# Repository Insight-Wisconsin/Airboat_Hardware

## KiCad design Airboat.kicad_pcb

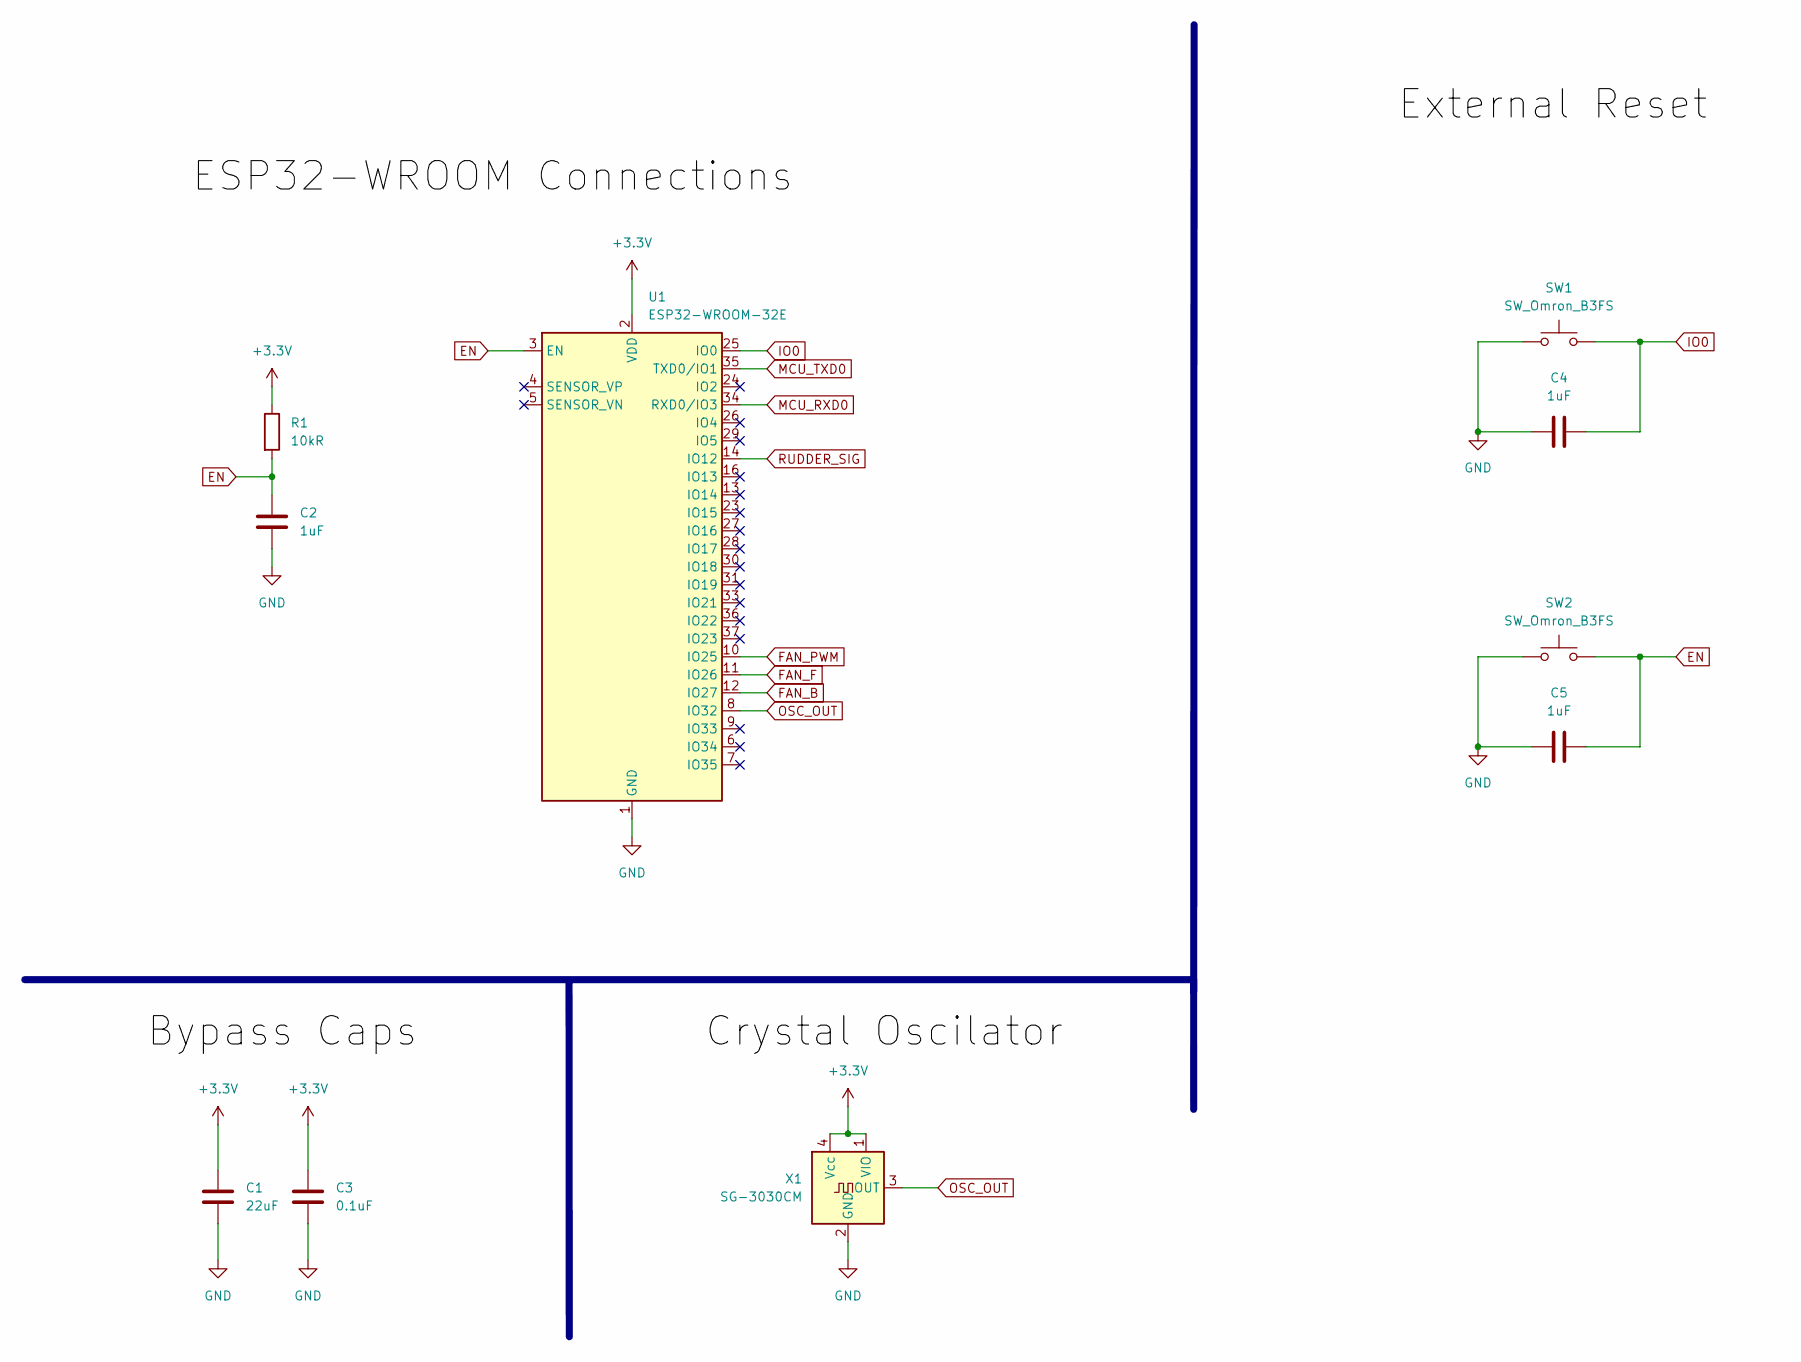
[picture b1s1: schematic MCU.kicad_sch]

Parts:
C1: 22uF; C_0603_1608Metric_Pad1.08x0.95mm_HandSolder
C2, C4, C5: 1uF; C_0603_1608Metric_Pad1.08x0.95mm_HandSolder
C3: 0.1uF; C_0603_1608Metric_Pad1.08x0.95mm_HandSolder
R1: 10kR; R_0603_1608Metric_Pad0.98x0.95mm_HandSolder
SW1, SW2: SW_Omron_B3FS; SW_SPST_Omron_B3FS-100xP
U1: ESP32-WROOM-32E; ESP32-WROOM-32D
X1: SG-3030CM; Oscillator_SMD_SeikoEpson_SG3030CM

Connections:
+3.3V: C1.1, C3.1, R1.1, U1.2 (VDD), X1.1 (VIO), X1.4 (Vcc); also elsewhere on the board
EN: C2.1, C5.2, R1.2, SW2.2, U1.3 (EN); also elsewhere on the board
FAN_B: U1.12 (IO27); also elsewhere on the board
FAN_F: U1.11 (IO26); also elsewhere on the board
FAN_PWM: U1.10 (IO25); also elsewhere on the board
GND: C1.2, C2.2, C3.2, C4.1, C5.1, SW1.1, SW2.1, U1.1 (GND), U1.15 (GND), U1.38 (GND), U1.39 (GND), X1.2 (GND); also elsewhere on the board
IO0: C4.2, SW1.2, U1.25 (IO0); also elsewhere on the board
MCU_RXD0: U1.34 (RXD0/IO3); also elsewhere on the board
MCU_TXD0: U1.35 (TXD0/IO1); also elsewhere on the board
OSC_OUT: U1.8 (IO32), X1.3 (OUT)
RUDDER_SIG: U1.14 (IO12); also elsewhere on the board

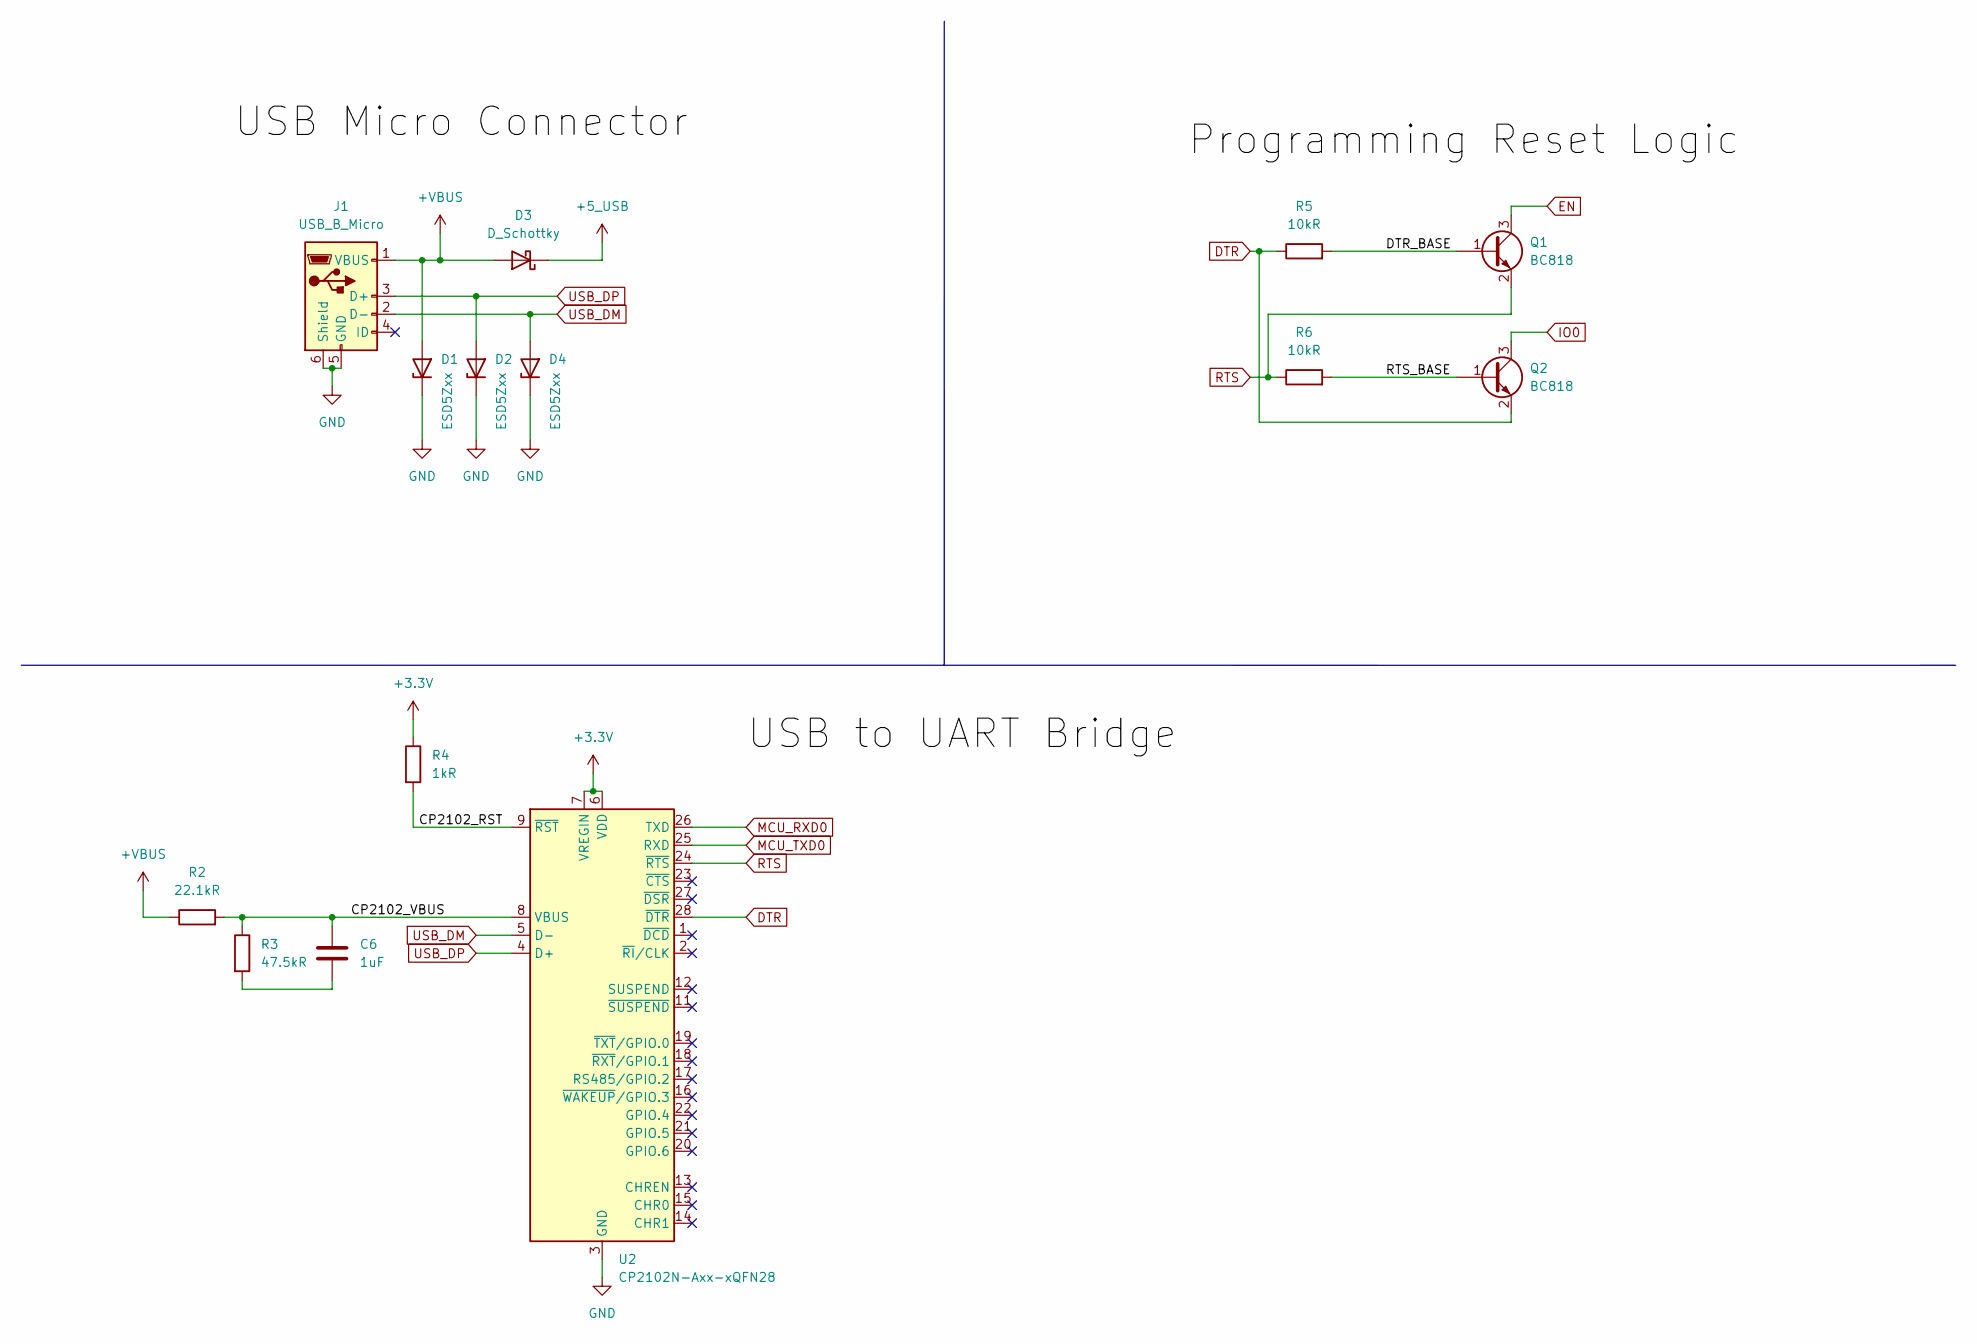
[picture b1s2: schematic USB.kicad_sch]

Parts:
C6: 1uF; C_0603_1608Metric_Pad1.08x0.95mm_HandSolder
D1, D2, D4: ESD5Zxx; D_SOD-523
D3: D_Schottky; D_SMC
J1: USB_B_Micro; USB_Micro-B_GCT_USB3076-30-A
Q1, Q2: BC818; SOT-23
R2: 22.1kR; R_0603_1608Metric_Pad0.98x0.95mm_HandSolder
R3: 47.5kR; R_0603_1608Metric_Pad0.98x0.95mm_HandSolder
R4: 1kR; R_0603_1608Metric_Pad0.98x0.95mm_HandSolder
R5, R6: 10kR; R_0603_1608Metric_Pad0.98x0.95mm_HandSolder
U2: CP2102N-Axx-xQFN28; QFN-28-1EP_5x5mm_P0.5mm_EP3.75x3.75mm

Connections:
+3.3V: R4.1, U2.6 (VDD), U2.7 (VREGIN); also elsewhere on the board
+5_USB: D3.1 (K); also elsewhere on the board
+VBUS: D1.2 (A), D3.2 (A), J1.1 (VBUS), R2.1
/USB/CP2102_RST: R4.2, U2.9 (~RST)
/USB/CP2102_VBUS: C6.1, R2.2, R3.1, U2.8 (VBUS)
/USB/DTR_BASE: Q1.1 (B), R5.2
/USB/RTS_BASE: Q2.1 (B), R6.2
DTR: Q2.2 (E), R5.1, U2.28 (~DTR)
EN: Q1.3 (C); also elsewhere on the board
GND: D1.1 (K), D2.1 (K), D4.1 (K), J1.5 (GND), J1.6 (Shield), U2.3 (GND), U2.29 (GND); also elsewhere on the board
IO0: Q2.3 (C); also elsewhere on the board
MCU_RXD0: U2.26 (TXD); also elsewhere on the board
MCU_TXD0: U2.25 (RXD); also elsewhere on the board
unnamed: C6.2, R3.2
RTS: Q1.2 (E), R6.1, U2.24 (~RTS)
USB_DM: D4.2 (A), J1.2 (D-), U2.5 (D-)
USB_DP: D2.2 (A), J1.3 (D+), U2.4 (D+)

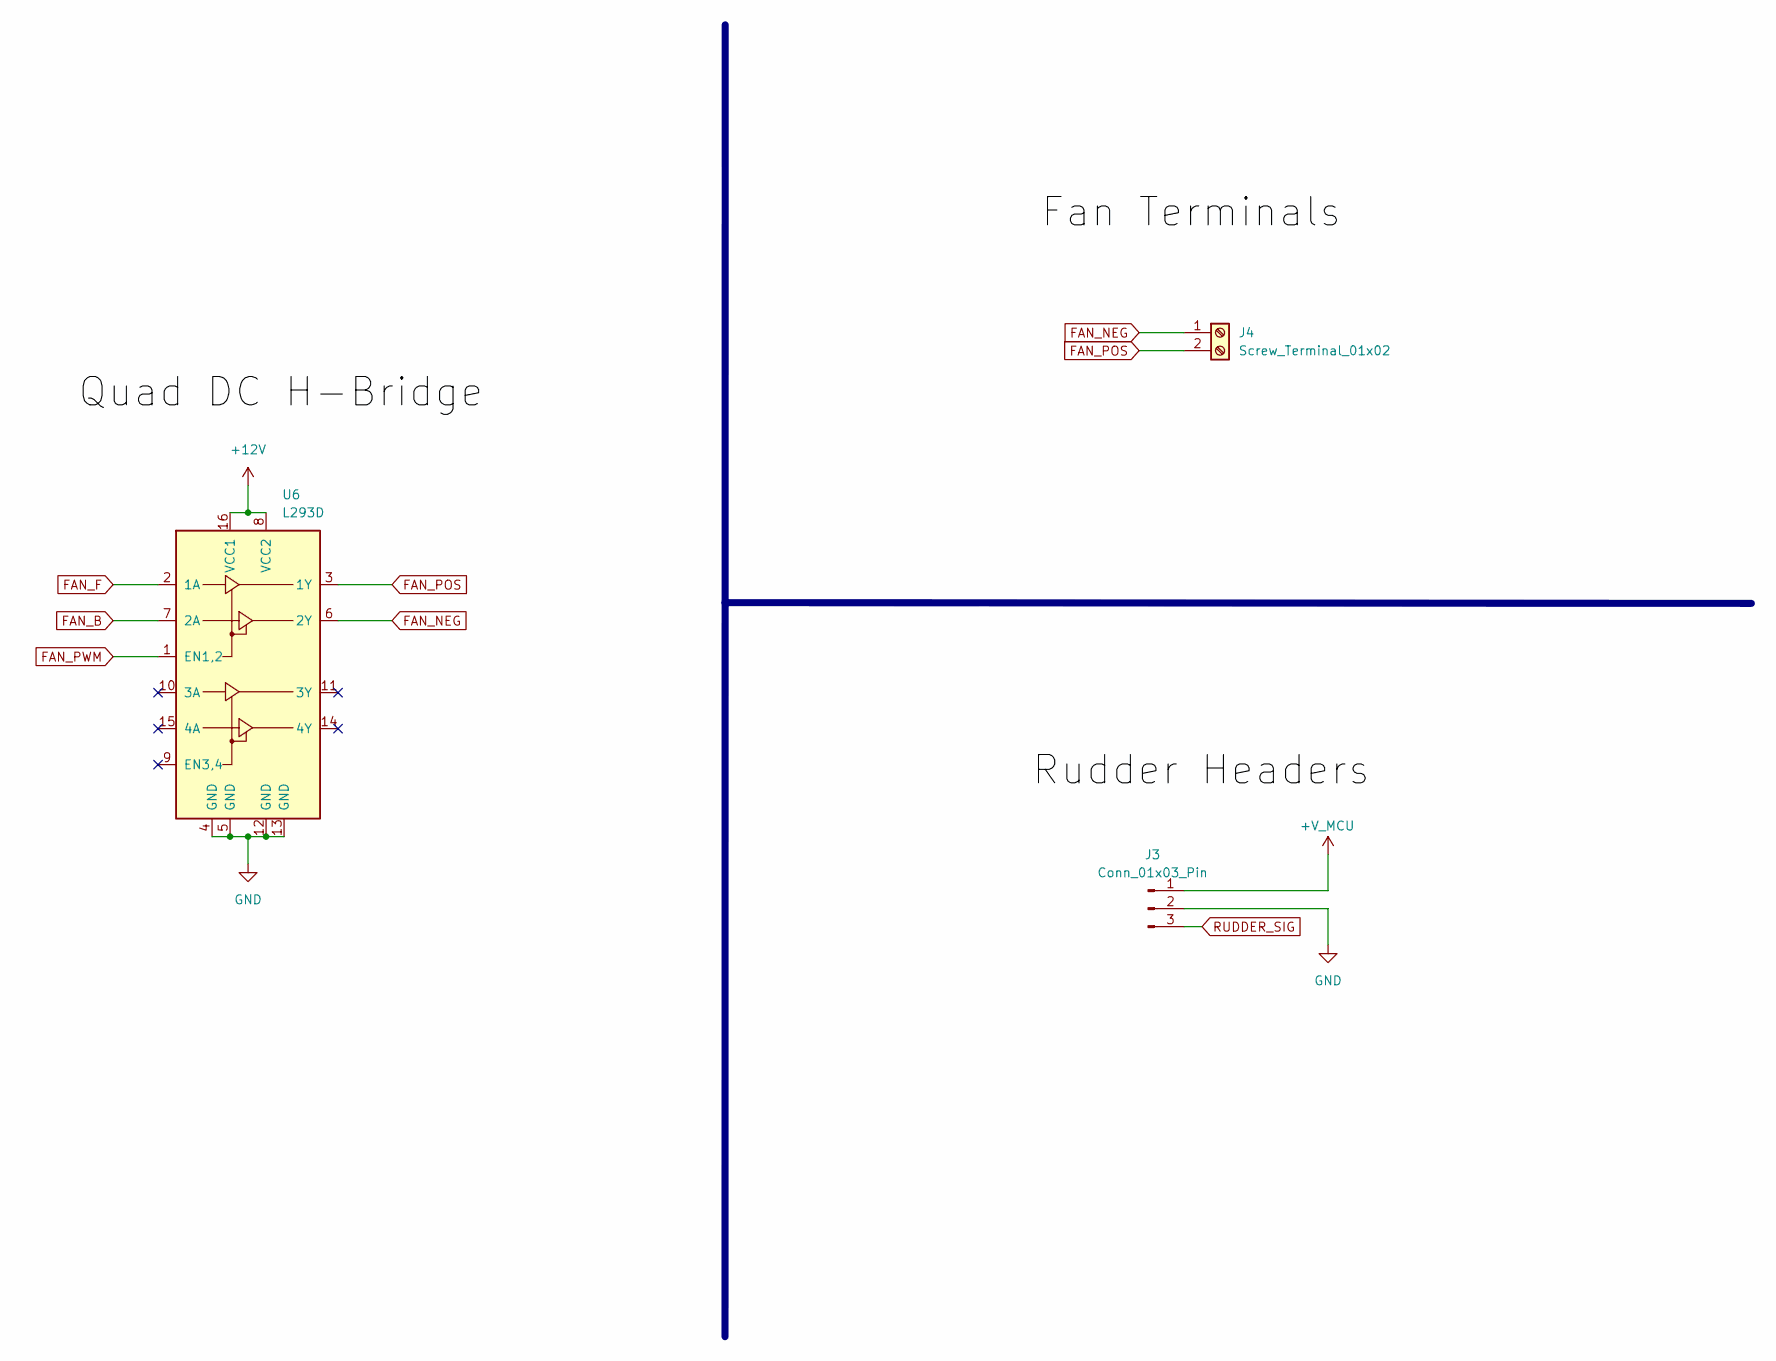
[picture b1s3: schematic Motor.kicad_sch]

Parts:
J3: Conn_01x03_Pin; FanPinHeader_1x03_P2.54mm_Vertical
J4: Screw_Terminal_01x02; TerminalBlock_Altech_AK300-2_P5.00mm
U6: L293D; DIP-16_W7.62mm

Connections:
+12V: U6.8 (VCC2), U6.16 (VCC1); also elsewhere on the board
+V_MCU: J3.1; also elsewhere on the board
FAN_B: U6.7 (2A); also elsewhere on the board
FAN_F: U6.2 (1A); also elsewhere on the board
FAN_NEG: J4.1, U6.6 (2Y)
FAN_POS: J4.2, U6.3 (1Y)
FAN_PWM: U6.1 (EN1,2); also elsewhere on the board
GND: J3.2, U6.4 (GND), U6.5 (GND), U6.12 (GND), U6.13 (GND); also elsewhere on the board
RUDDER_SIG: J3.3; also elsewhere on the board

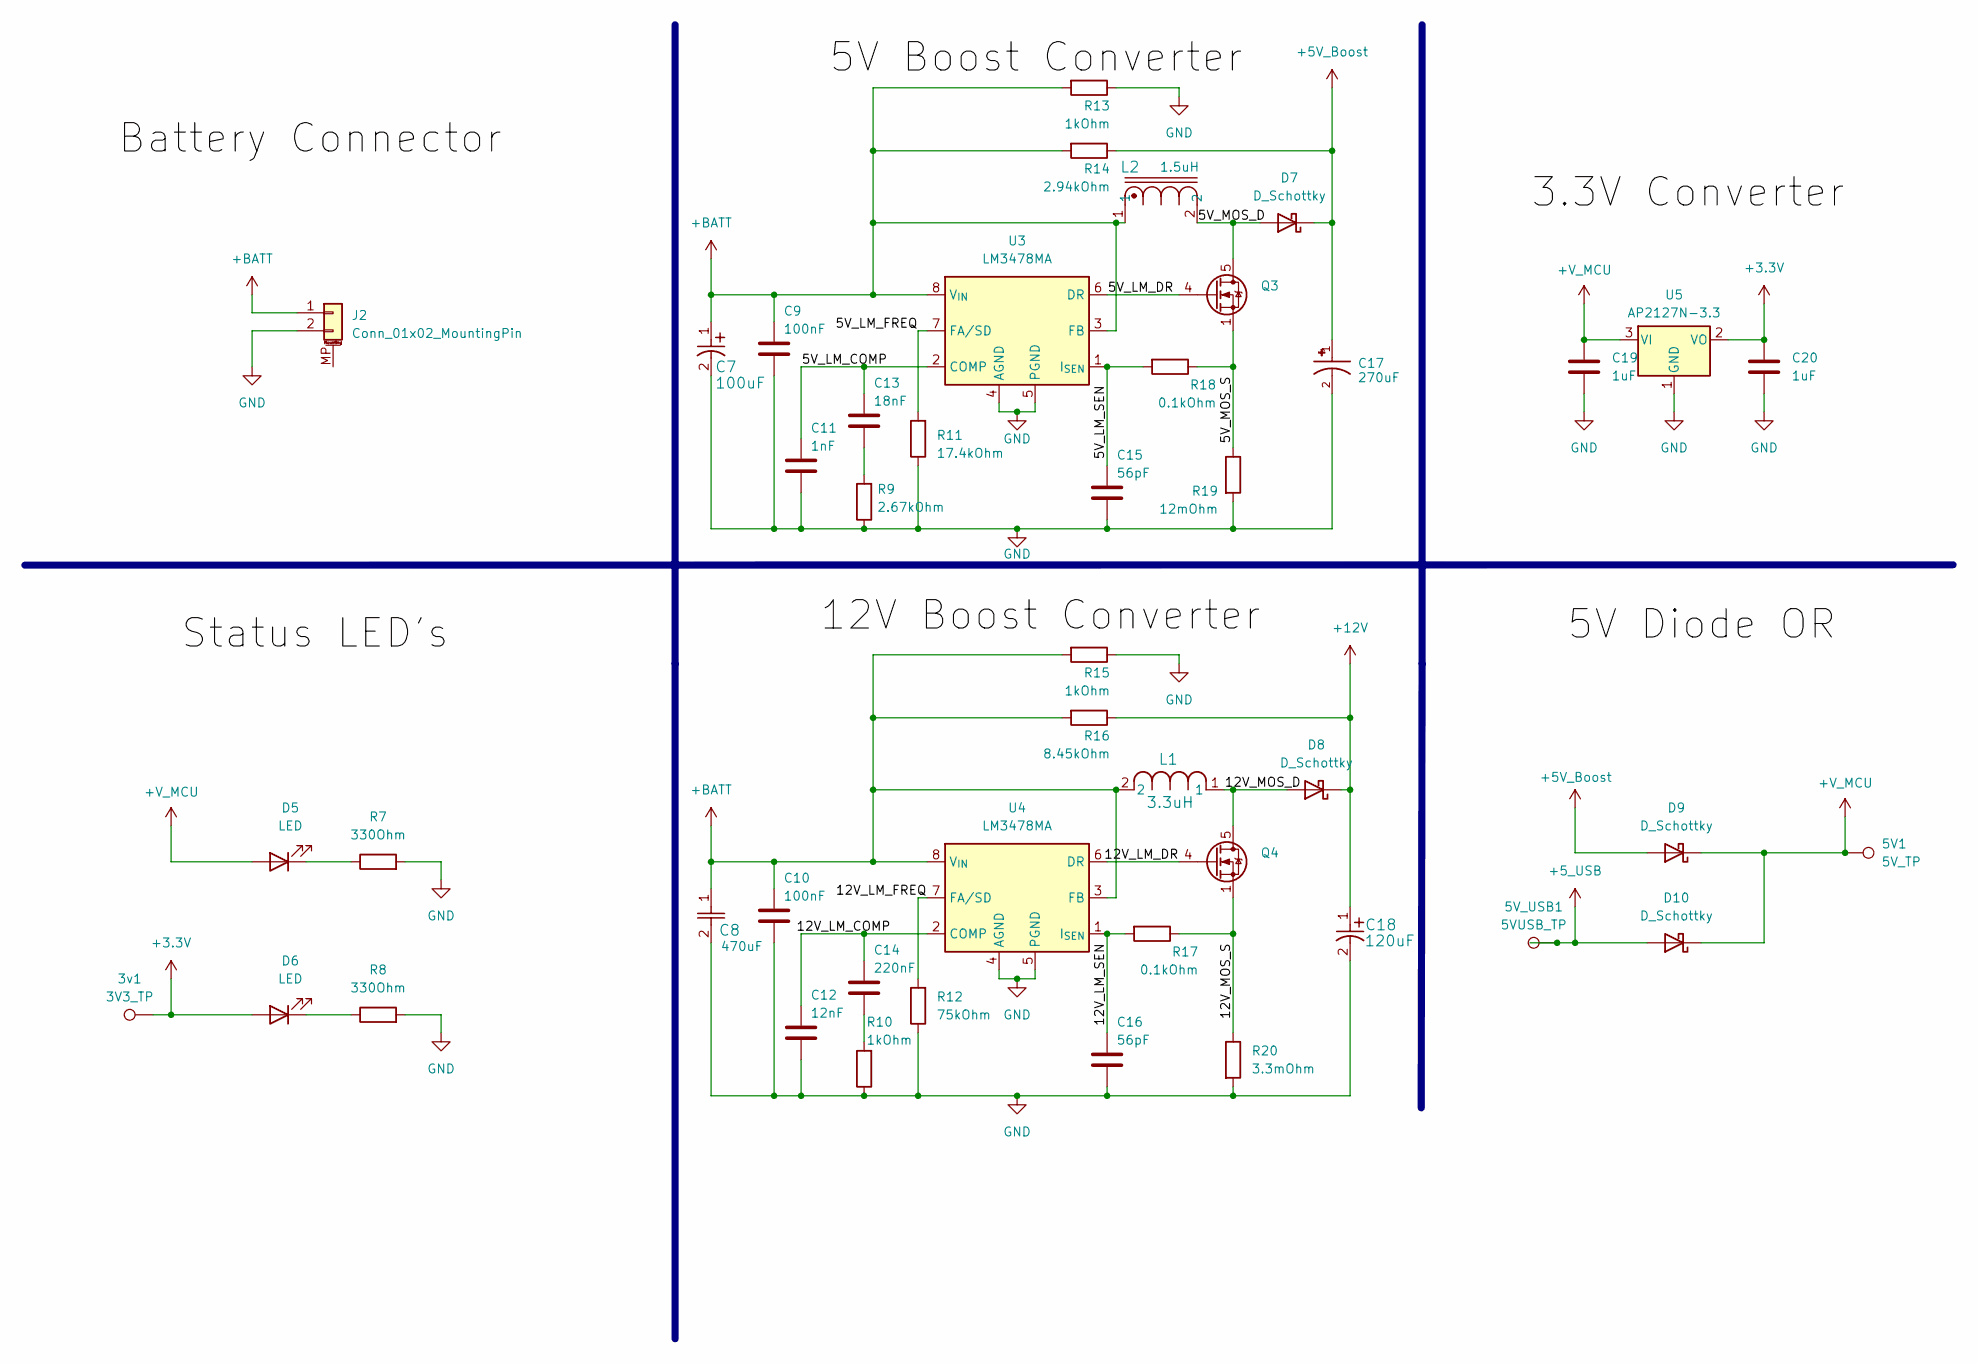
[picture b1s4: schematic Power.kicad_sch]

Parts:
3v1: 3V3_TP; TestPoint_Pad_D2.0mm
5V1: 5V_TP; TestPoint_Pad_D2.0mm
5V_USB1: 5VUSB_TP; TestPoint_Pad_D2.0mm
C7: T520A107M006ATE025; CAPMP3.4X1.6_1.8N_KEM
C8: UUD1E471MNL1GS; U2-R_NCH
C9, C10: 100nF; C_0603_1608Metric_Pad1.08x0.95mm_HandSolder
C11: 1nF; C_0603_1608Metric_Pad1.08x0.95mm_HandSolder
C12: 12nF; C_0603_1608Metric_Pad1.08x0.95mm_HandSolder
C13: 18nF; C_0603_1608Metric_Pad1.08x0.95mm_HandSolder
C14: 220nF; C_0603_1608Metric_Pad1.08x0.95mm_HandSolder
C15, C16: 56pF; C_0603_1608Metric_Pad1.08x0.95mm_HandSolder
C17: 16SVPG270M; CAP_16SVPG270M; PARTREV 05-Mar-21
C18: 20SVPF120M; PCAP_SVP_C6_PAN
C19, C20: 1uF; C_0603_1608Metric_Pad1.08x0.95mm_HandSolder
D5, D6: LED; LED_0805_2012Metric_Pad1.15x1.40mm_HandSolder
D7, D8, D9, D10: D_Schottky; D_SMC
J2: Conn_01x02_MountingPin; Hirose_DF3EA-02P-2H_1x02-1MP_P2.00mm_Horizontal
L1: IHLP6767GZER3R3M51; IND_IHLP-6767GZ_VIS
L2: DR1040-1R5-R; DR1040
Q3, Q4: CSD16321Q5; TDSON-8-1
R7, R8: 330Ohm; R_0603_1608Metric_Pad0.98x0.95mm_HandSolder
R9: 2.67kOhm; R_0603_1608Metric_Pad0.98x0.95mm_HandSolder
R10, R13, R15: 1kOhm; R_0603_1608Metric_Pad0.98x0.95mm_HandSolder
R11: 17.4kOhm; R_0603_1608Metric_Pad0.98x0.95mm_HandSolder
R12: 75kOhm; R_0603_1608Metric_Pad0.98x0.95mm_HandSolder
R14: 2.94kOhm; R_0603_1608Metric_Pad0.98x0.95mm_HandSolder
R16: 8.45kOhm; R_0603_1608Metric_Pad0.98x0.95mm_HandSolder
R17, R18: 0.1kOhm; R_0603_1608Metric_Pad0.98x0.95mm_HandSolder
R19: 12mOhm; R_0603_1608Metric_Pad0.98x0.95mm_HandSolder
R20: 3.3mOhm; R_2512_6332Metric_Pad1.40x3.35mm_HandSolder
U3, U4: LM3478MA; SOIC-8_3.9x4.9mm_P1.27mm
U5: AP2127N-3.3; SOT-23

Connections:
+3.3V: 3v1.1, C20.1, D6.2 (A), U5.2 (VO); also elsewhere on the board
+5V_Boost: C17.1, D7.1 (K), D9.2 (A), R14.1
+5_USB: 5V_USB1.1, D10.2 (A); also elsewhere on the board
+12V: C18.1, D8.1 (K), R16.1; also elsewhere on the board
+BATT: C7.1, C8.1, C9.1, C10.1, J2.1, L1.2, L2.1, R13.2, R14.2, R15.2, R16.2, U3.3 (FB), U3.8 (V_{IN}), U4.3 (FB), U4.8 (V_{IN})
+V_MCU: 5V1.1, C19.1, D5.2 (A), D9.1 (K), D10.1 (K), U5.3 (VI); also elsewhere on the board
/Power/5V_LM_COMP: C11.1, C13.1, U3.2 (COMP)
/Power/5V_LM_DR: Q3.4 (G), U3.6 (DR)
/Power/5V_LM_FREQ: R11.2, U3.7 (FA/SD)
/Power/5V_LM_SEN: C15.1, R18.2, U3.1 (I_{SEN})
/Power/5V_MOS_D: D7.2 (A), L2.2, Q3.5 (D)
/Power/5V_MOS_S: Q3.1 (S), Q3.2 (S), Q3.3 (S), R18.1, R19.1
/Power/12V_LM_COMP: C12.1, C14.1, U4.2 (COMP)
/Power/12V_LM_DR: Q4.4 (G), U4.6 (DR)
/Power/12V_LM_FREQ: R12.2, U4.7 (FA/SD)
/Power/12V_LM_SEN: C16.1, R17.2, U4.1 (I_{SEN})
/Power/12V_MOS_D: D8.2 (A), L1.1, Q4.5 (D)
/Power/12V_MOS_S: Q4.1 (S), Q4.2 (S), Q4.3 (S), R17.1, R20.1
GND: C7.2, C8.2, C9.2, C10.2, C11.2, C12.2, C15.2, C16.2, C17.2, C18.2, C19.2, C20.2, J2.2, R7.2, R8.2, R9.1, R10.1, R11.1, R12.1, R13.1, R15.1, R19.2, R20.2, U3.4 (AGND), U3.5 (PGND), U4.4 (AGND), U4.5 (PGND), U5.1 (GND); also elsewhere on the board
unnamed: C13.2, R9.2
unnamed: C14.2, R10.2
unnamed: D5.1 (K), R7.1
unnamed: D6.1 (K), R8.1

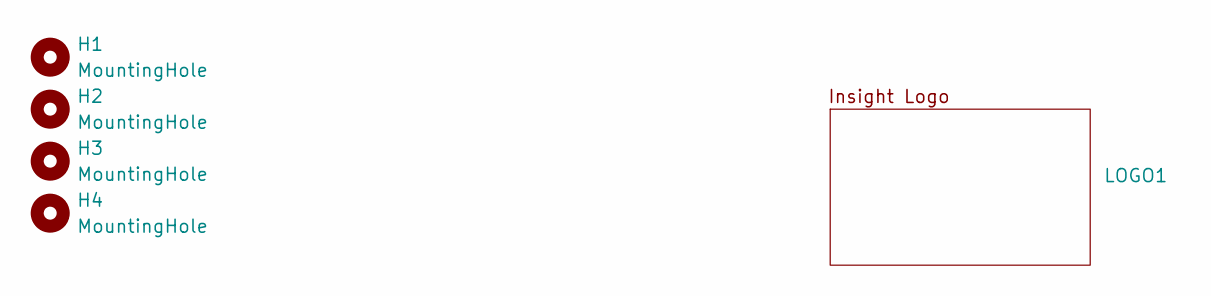
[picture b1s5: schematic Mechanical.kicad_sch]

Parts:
H1, H2, H3, H4: MountingHole; MountingHole_2.2mm_M2
LOGO1: Insight_Logo

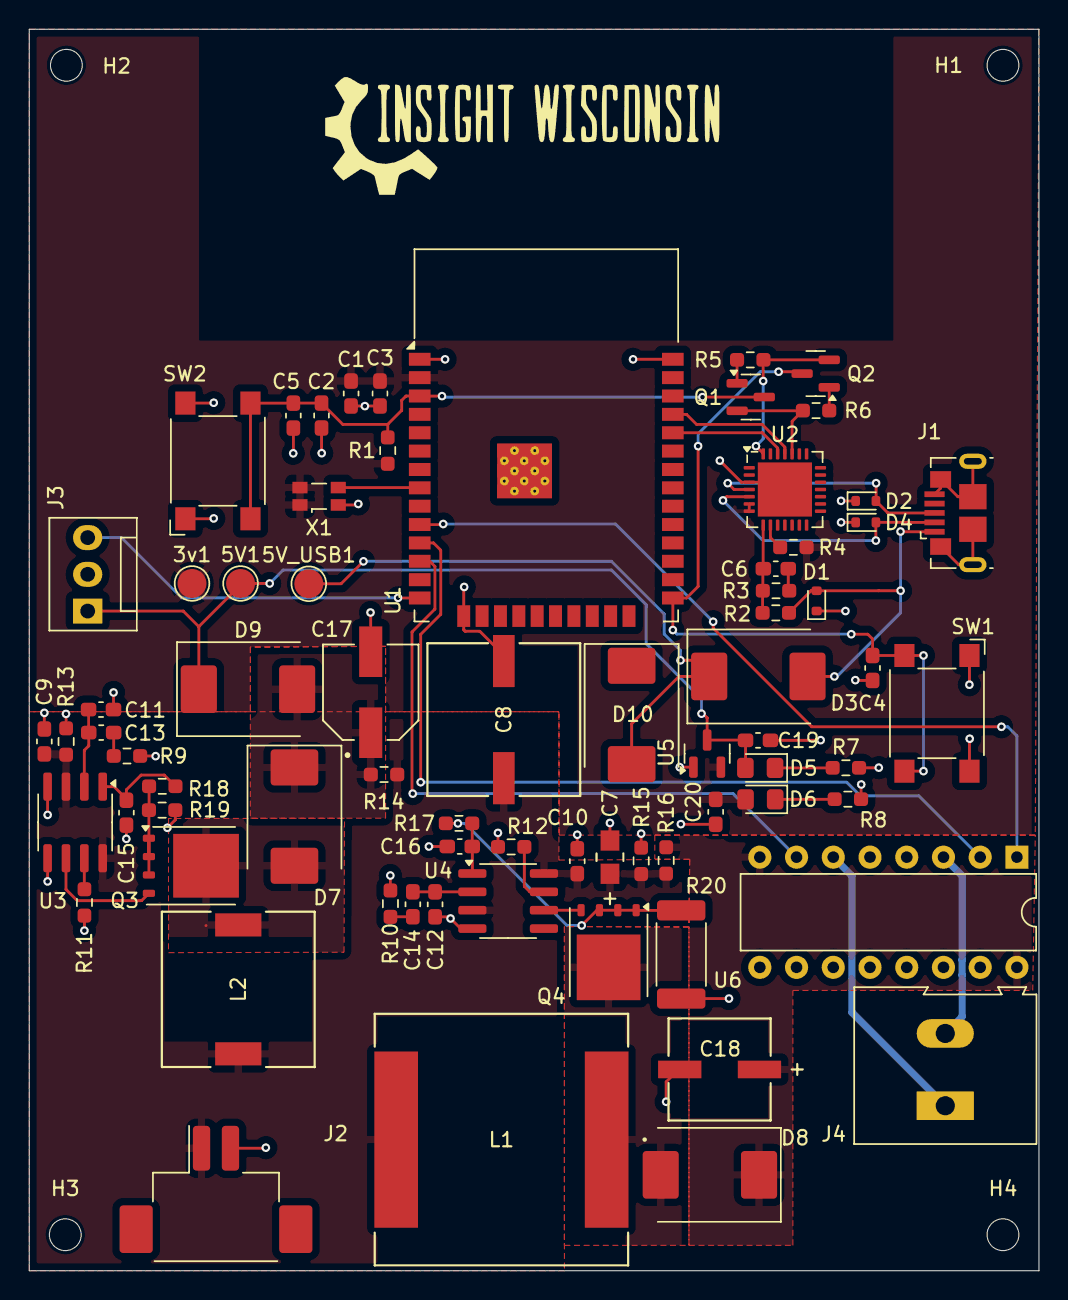
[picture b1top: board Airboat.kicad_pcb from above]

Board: 2 copper layers, 69.8 x 85.9 mm, 77 parts (0 on the bottom side), 44 nets.

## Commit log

2024-08-12 Inital commit of kicad files
2024-08-12 Finished Updating Schematics
2024-08-12 Fixed PCB errors
2024-08-12 Started to layout PCB
2024-08-12 Placed all components on PCB
2024-08-13 Removed uneeeded components, started to lay PCB traces
2024-08-13 Finished PCB routing
2024-09-17 Updated PCB to be smaller and support stepper
2024-11-05 Updated to use boost converters
2024-11-05 Updated .gitignore
